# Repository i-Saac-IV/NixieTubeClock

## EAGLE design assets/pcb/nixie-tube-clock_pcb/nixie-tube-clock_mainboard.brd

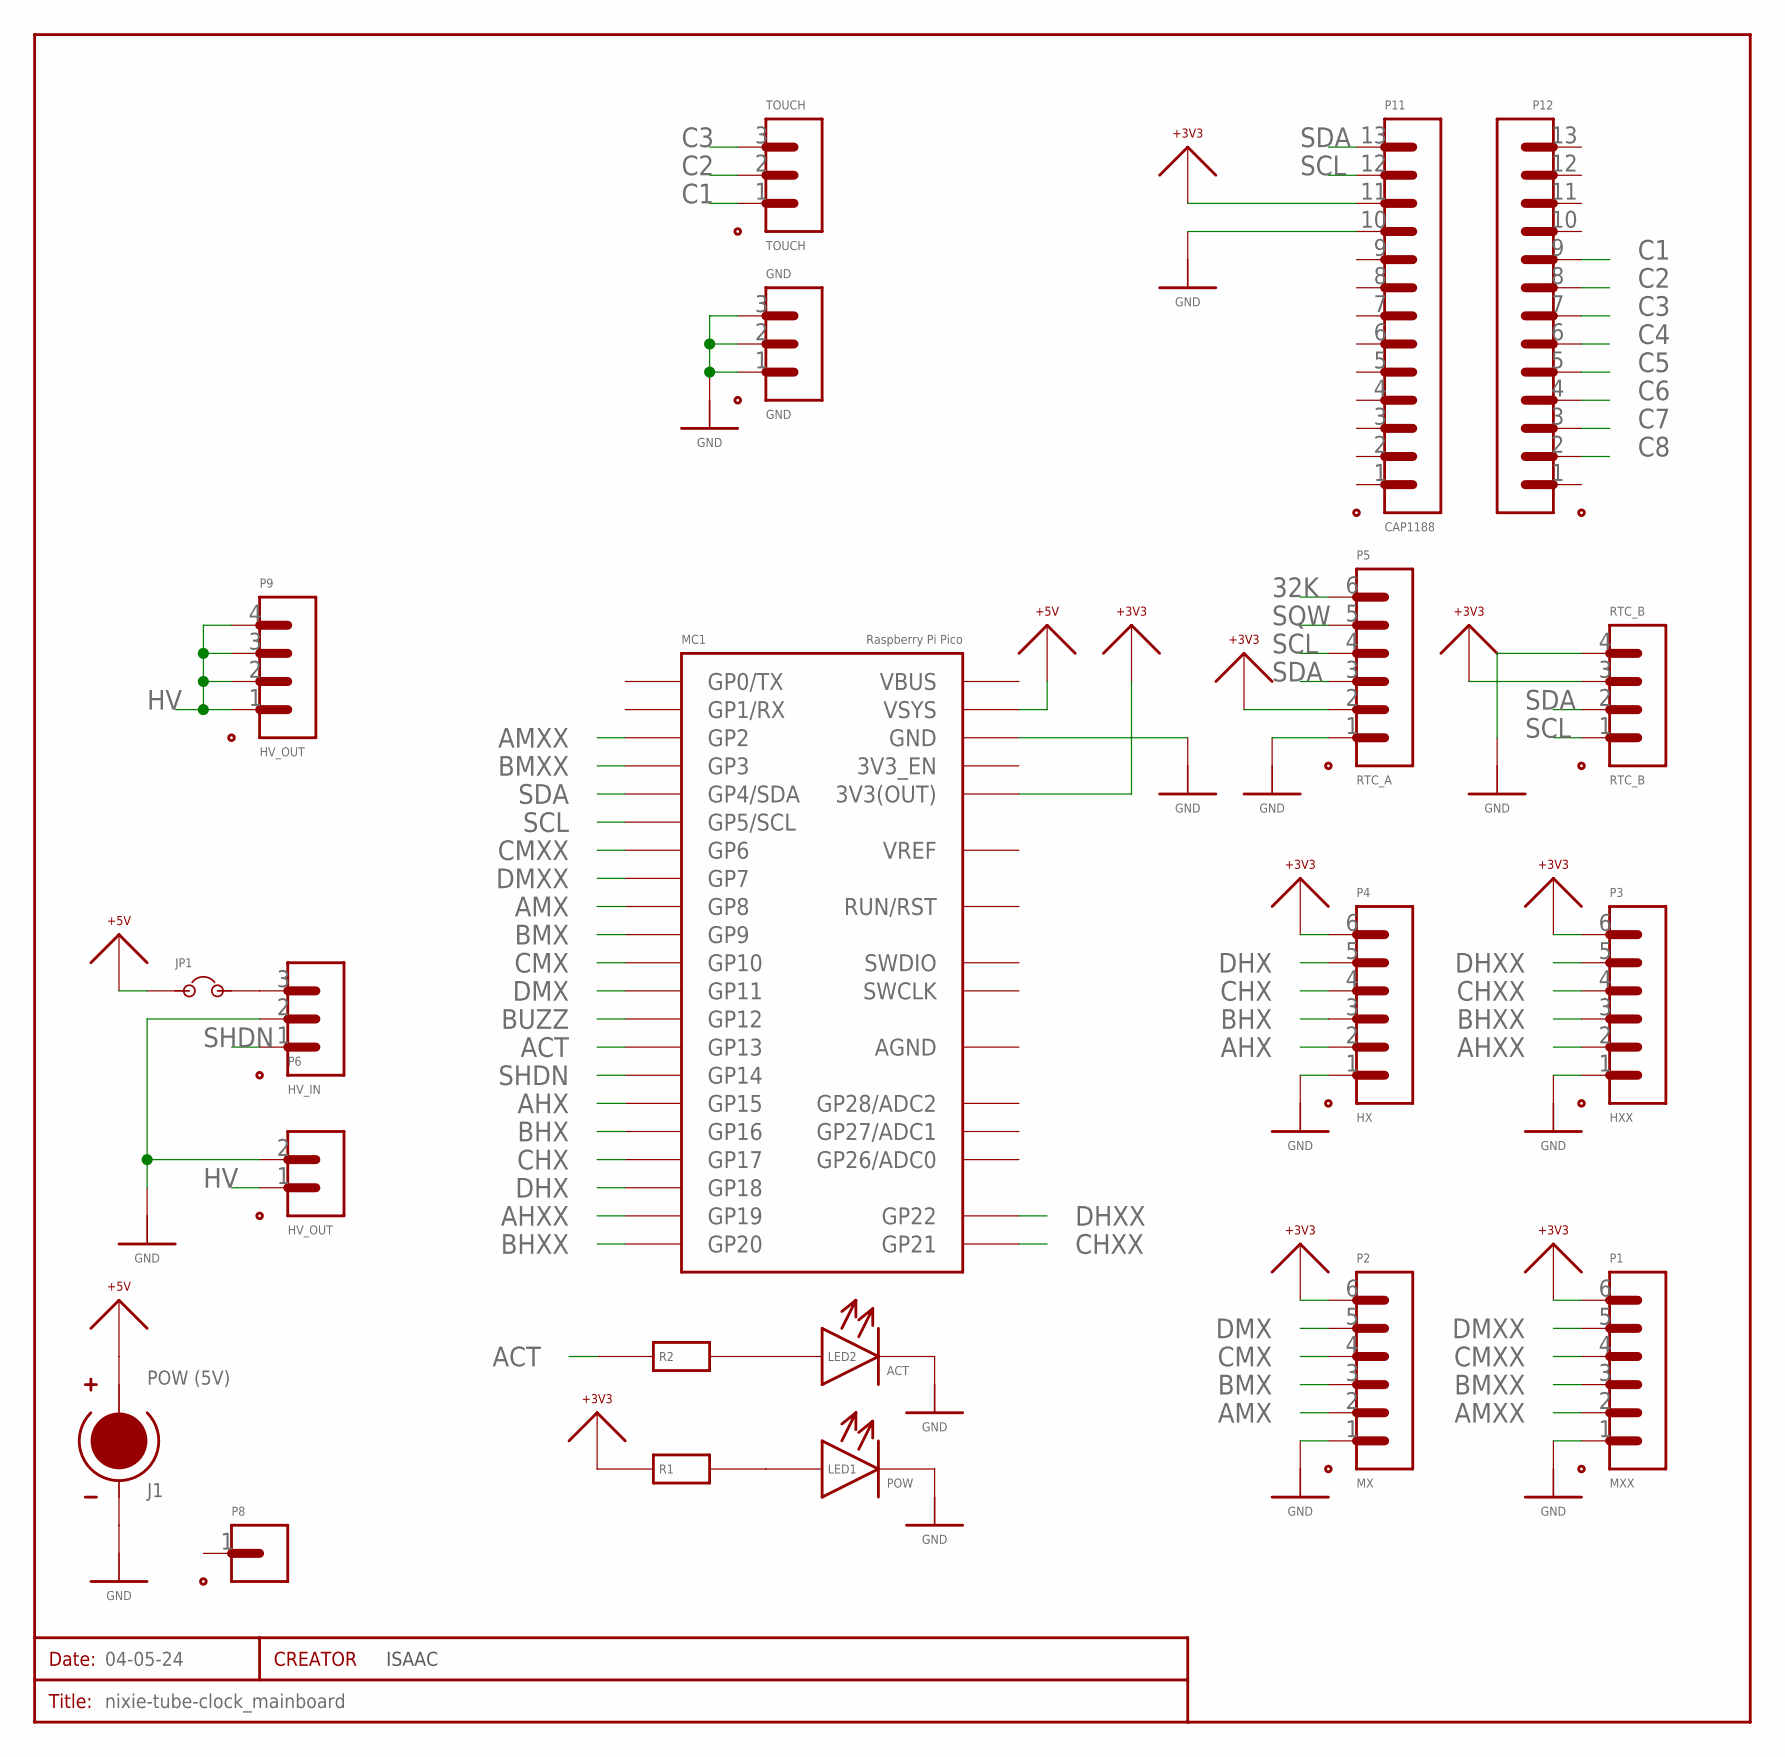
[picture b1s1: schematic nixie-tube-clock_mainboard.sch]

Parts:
CREATOR: ISAAC; INFO_T
GND: GND; XH2.54_3-PIN
J1: POW (5V); XH2.54_2-PIN
JP1: JUMPER_2-WAY_HEADER; HEADER_2-PIN_JUMPER
LED1: POW; LED_3MM
LED2: ACT; LED_3MM
MC1: RASPBERRY-PI-PICO_THT
P1: MXX; XH2.54_6-PIN
P2: MX; XH2.54_6-PIN
P3: HXX; XH2.54_6-PIN
P4: HX; XH2.54_6-PIN
P5: RTC_A; HEADER_6-PIN
P6: HV_OUT; HEADER_2-PIN
P7: HV_IN; HEADER_3-PIN
P8: PORT_1-PIN_HEADER; HEADER_1-PIN
P9: HV_OUT; XH2.54_4-PIN
P11: CAP1188; HEADER_13-PIN
P12: PORT_13-PIN_HEADER; HEADER_13-PIN
R1, R2: RESISTOR; RESISTOR_10.16MM
RTC_B: RTC_B; XH2.54_4-PIN
SCHEMATIC1: 04-05-24; SHEET
TOUCH: TOUCH; XH2.54_3-PIN

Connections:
32K: P5.6
+3V3: MC1.36 (3V3(OUT)), P1.6, P2.6, P3.6, P4.6, P5.2, P11.11, R1.1, RTC_B.3
+5V: J1.2 (+), JP1.1, MC1.39 (VSYS)
ACT: MC1.17 (GP13), R2.1
AGND: MC1.33 (AGND)
AHX: MC1.20 (GP15), P4.2
AHXX: MC1.25 (GP19), P3.2
AMX: MC1.11 (GP8), P2.2
AMXX: MC1.4 (GP2), P1.2
BHX: MC1.21 (GP16), P4.3
BHXX: MC1.26 (GP20), P3.3
BMX: MC1.12 (GP9), P2.3
BMXX: MC1.5 (GP3), P1.3
BUZZ: MC1.16 (GP12)
C1: P12.9, TOUCH.1
C2: P12.8, TOUCH.2
C3: P12.7, TOUCH.3
C4: P12.6
C5: P12.5
C6: P12.4
C7: P12.3
C8: P12.2
CHX: MC1.22 (GP17), P4.4
CHXX: MC1.27 (GP21), P3.4
CMX: MC1.14 (GP10), P2.4
CMXX: MC1.9 (GP6), P1.4
DHX: MC1.24 (GP18), P4.5
DHXX: MC1.29 (GP22), P3.5
DMX: MC1.15 (GP11), P2.5
DMXX: MC1.10 (GP7), P1.5
GND: GND.1, GND.2, GND.3, J1.1 (GND), LED1.-, LED2.-, MC1.3 (GND), MC1.8 (GND), MC1.13 (GND), MC1.18 (GND), MC1.23 (GND), MC1.28 (GND), MC1.38 (GND), MC1.D_GND (GND), P1.1, P2.1, P3.1, P4.1, P5.1, P6.2, P7.2, P11.10, RTC_B.4
HV: P6.1, P9.1, P9.2, P9.3, P9.4
unnamed: LED1.+, R1.2
unnamed: LED2.+, R2.2
unnamed: JP1.2, P7.3
SCL: MC1.7 (GP5/SCL), P5.4, P11.12, RTC_B.1
SDA: MC1.6 (GP4/SDA), P5.3, P11.13, RTC_B.2
SHDN: MC1.19 (GP14), P7.1
SQW: P5.5

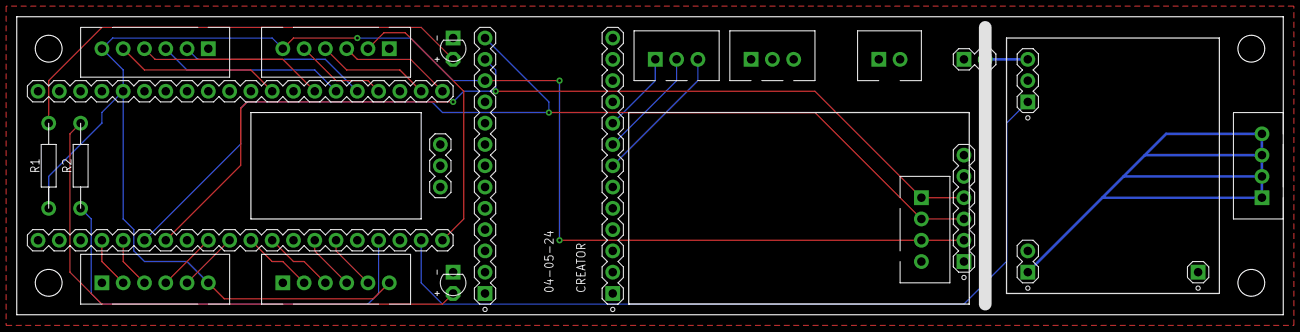
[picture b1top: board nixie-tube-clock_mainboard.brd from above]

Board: 2 copper layers, 151.1 x 35.6 mm, 23 parts (0 on the bottom side), 30 nets.

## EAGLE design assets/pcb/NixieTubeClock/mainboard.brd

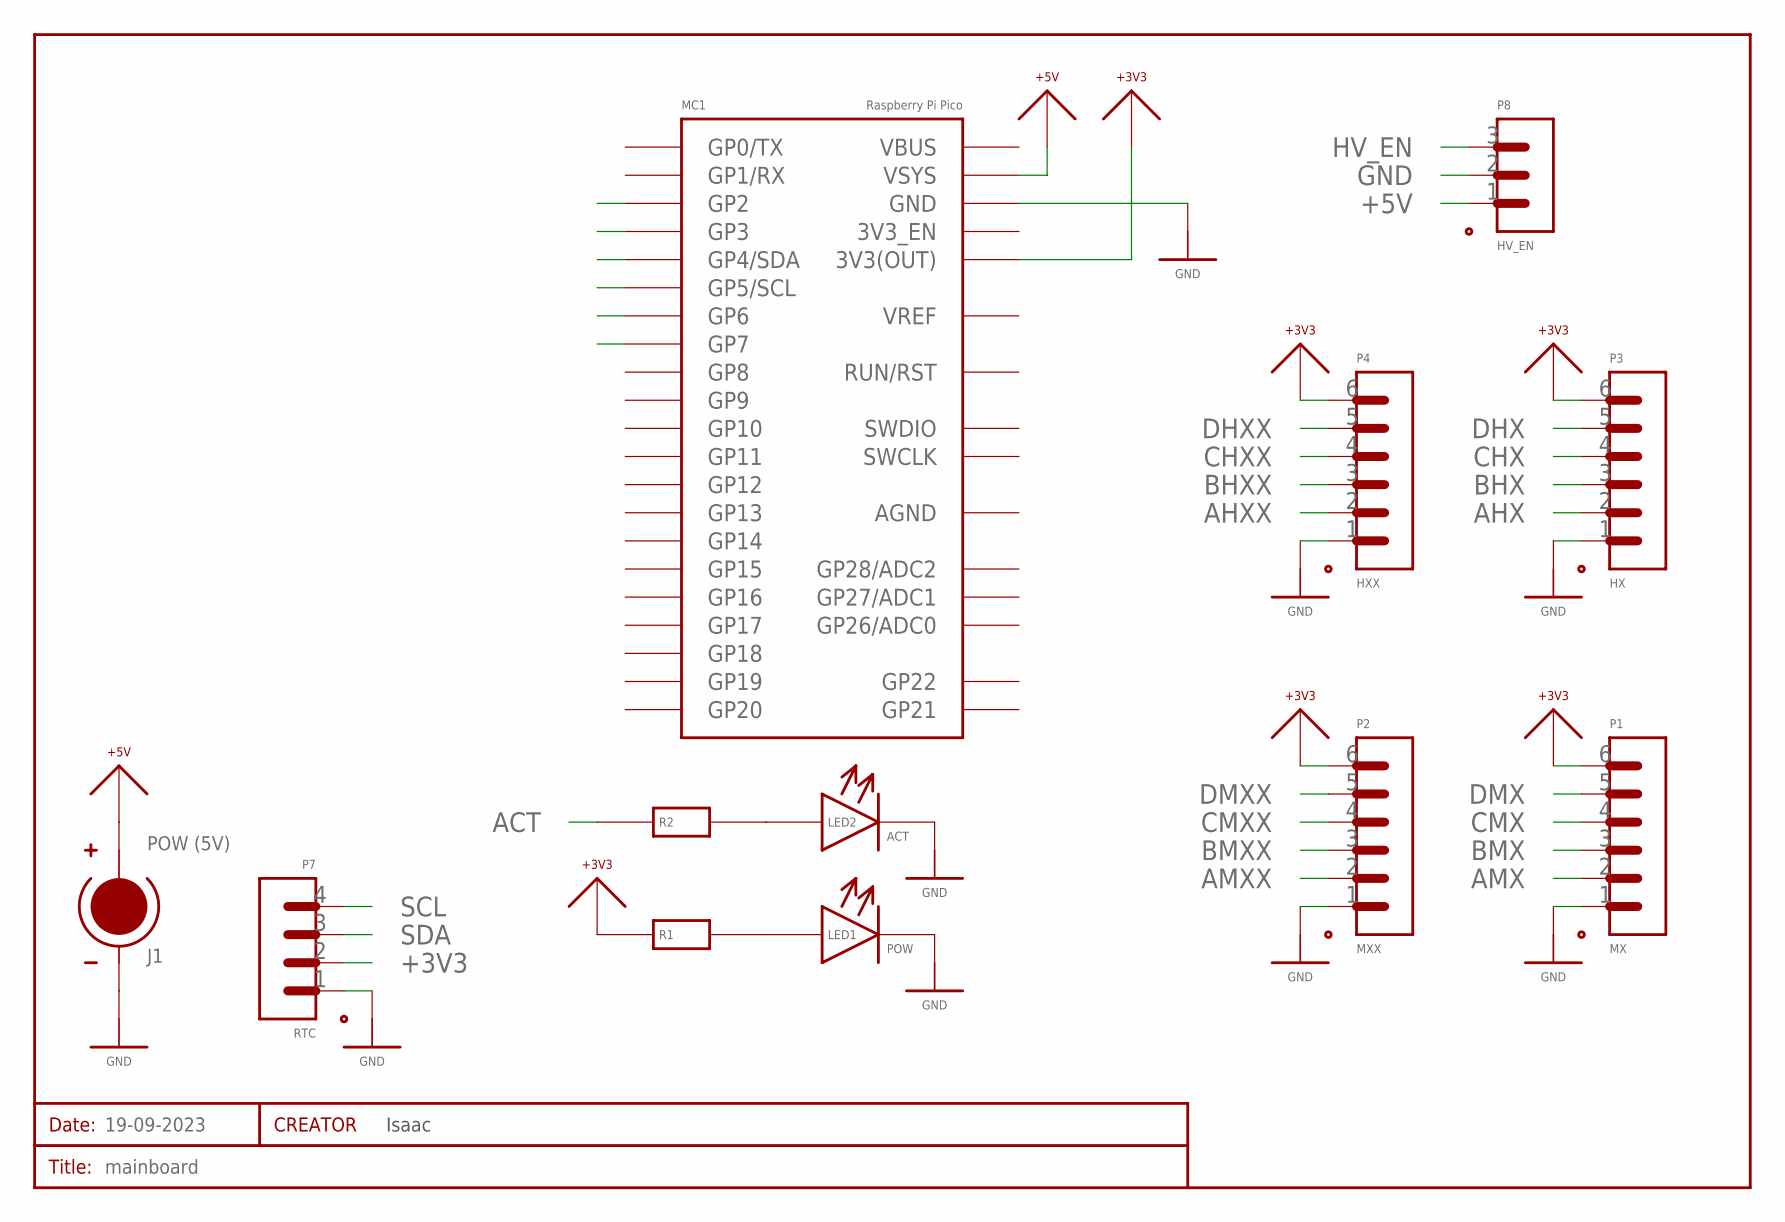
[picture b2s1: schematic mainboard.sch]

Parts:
CREATOR: Isaac; INFO_T
J1: POW (5V); XH2.54_2-PIN
LED1: POW; LED_3MM
LED2: ACT; LED_3MM
MC1: RASPBERRY-PI-PICO_THT
P1: MX; XH2.54_6-PIN
P2: MXX; XH2.54_6-PIN
P3: HX; XH2.54_6-PIN
P4: HXX; XH2.54_6-PIN
P7: RTC; XH2.54_4-PIN
P8: HV_EN; XH2.54_3-PIN
R1, R2: RESISTOR; RESISTOR_10.16MM
SCHEMATIC1: 19-09-2023; SHEET

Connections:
+3V3: MC1.36 (3V3(OUT)), P1.6, P2.6, P3.6, P4.6, P7.2, R1.1
+5V: J1.2 (+), MC1.39 (VSYS), P8.1
ACT: R2.1
AGND: MC1.33 (AGND)
AHX: P3.2
AHXX: P4.2
AMX: P1.2
AMXX: P2.2
BHX: P3.3
BHXX: P4.3
BMX: P1.3
BMXX: P2.3
CHX: P3.4
CHXX: P4.4
CMX: P1.4
CMXX: P2.4
DHX: P3.5
DHXX: P4.5
DMX: P1.5
DMXX: P2.5
GND: J1.1 (GND), LED1.-, LED2.-, MC1.3 (GND), MC1.8 (GND), MC1.13 (GND), MC1.18 (GND), MC1.23 (GND), MC1.28 (GND), MC1.38 (GND), MC1.D_GND (GND), P1.1, P2.1, P3.1, P4.1, P7.1, P8.2
HV_EN: P8.3
unnamed: LED1.+, R1.2
unnamed: LED2.+, R2.2
SCL: P7.4
SDA: P7.3

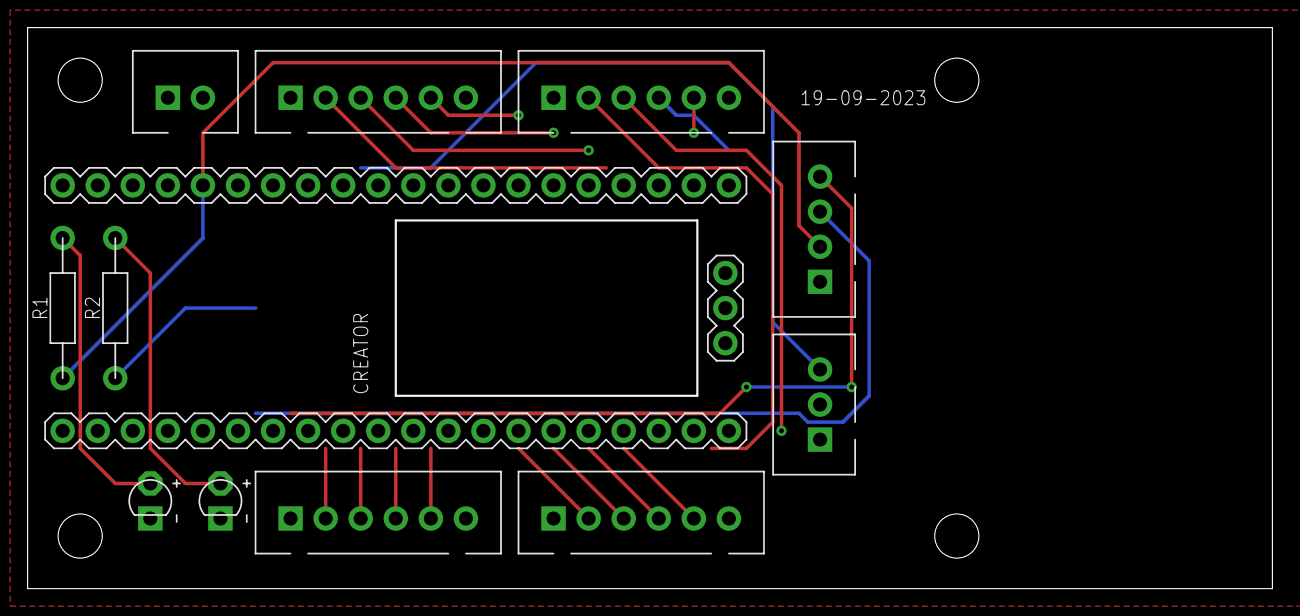
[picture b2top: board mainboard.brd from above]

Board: 2 copper layers, 90.0 x 40.5 mm, 14 parts (0 on the bottom side), 5 nets.

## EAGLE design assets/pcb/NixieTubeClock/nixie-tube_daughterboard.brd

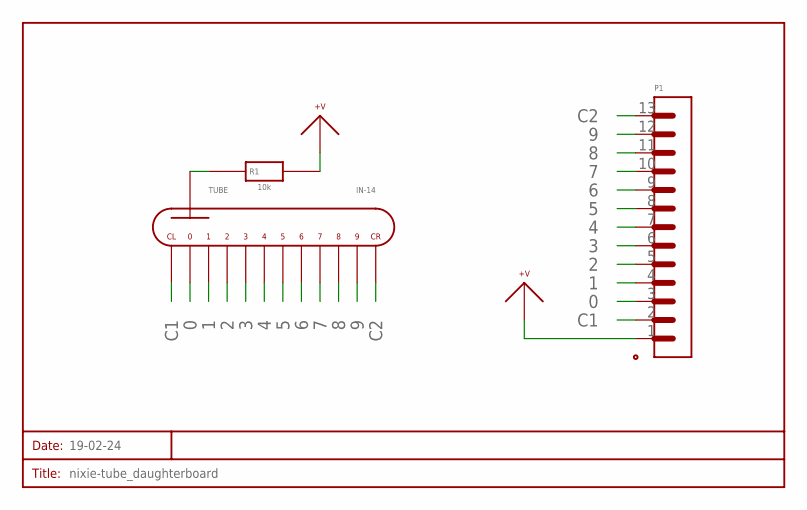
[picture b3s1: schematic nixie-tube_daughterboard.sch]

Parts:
P1: PORT_13-PIN_HEADER; HEADER_13-PIN
R1: 10k; RESISTOR_10.16MM
SCHEMATIC1: 19-02-24; SHEET
TUBE: IN-14; NIXIE-TUBE_IN-14

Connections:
0: P1.3, TUBE.0
1: P1.4, TUBE.1
2: P1.5, TUBE.2
3: P1.6, TUBE.3
4: P1.7, TUBE.4
5: P1.8, TUBE.5
6: P1.9, TUBE.6
7: P1.10, TUBE.7
8: P1.11, TUBE.8
9: P1.12, TUBE.9
+V: P1.1, R1.2
C1: P1.2, TUBE.C1
C2: P1.13, TUBE.C2
unnamed: R1.1, TUBE.A (ANODE)

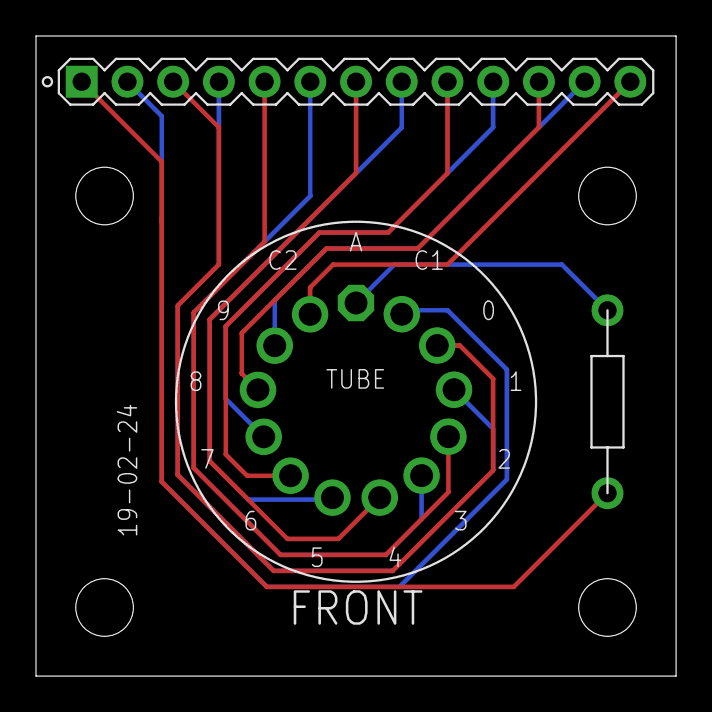
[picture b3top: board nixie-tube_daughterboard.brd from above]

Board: 2 copper layers, 35.6 x 35.6 mm, 4 parts (0 on the bottom side), 14 nets.

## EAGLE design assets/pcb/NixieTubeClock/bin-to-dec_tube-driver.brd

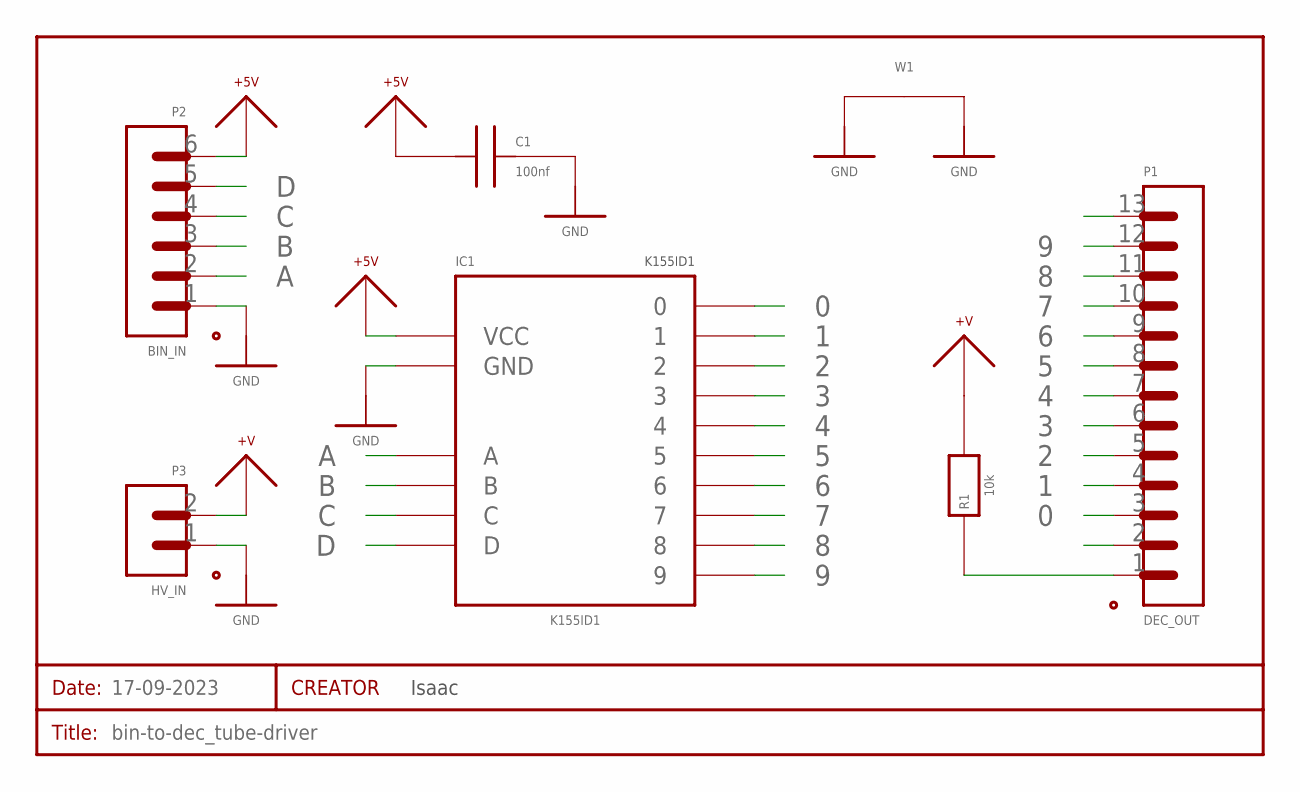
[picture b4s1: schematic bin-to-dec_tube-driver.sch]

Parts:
C1: 100nf; CAPACITOR_UNPOLARISED_5.08MM
CREATOR: Isaac; INFO_T
IC1: K155ID1; 16-PIN_DIP
P1: DEC_OUT; HEADER_13-PIN
P2: BIN_IN; XH2.54_6-PIN
P3: HV_IN; XH2.54_2-PIN
R1: 10k; RESISTOR_10.16MM
SCHEMATIC1: 17-09-2023; SHEET
W1: WIRE_7.62MM

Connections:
0: IC1.16 (0), P1.3
1: IC1.15 (1), P1.4
2: IC1.8 (2), P1.5
3: IC1.9 (3), P1.6
4: IC1.13 (4), P1.7
5: IC1.14 (5), P1.8
6: IC1.11 (6), P1.9
7: IC1.10 (7), P1.10
8: IC1.1 (8), P1.11
9: IC1.2 (9), P1.12
+5V: C1.1, IC1.5 (VCC), P2.6
+V: P3.2, R1.2
A: IC1.3 (A), P2.2
B: IC1.6 (B), P2.3
C: IC1.7 (C), P2.4
D: IC1.4 (D), P2.5
GND: C1.2, IC1.12 (GND), P2.1, P3.1, W1.1, W1.2
unnamed: P1.1, R1.1

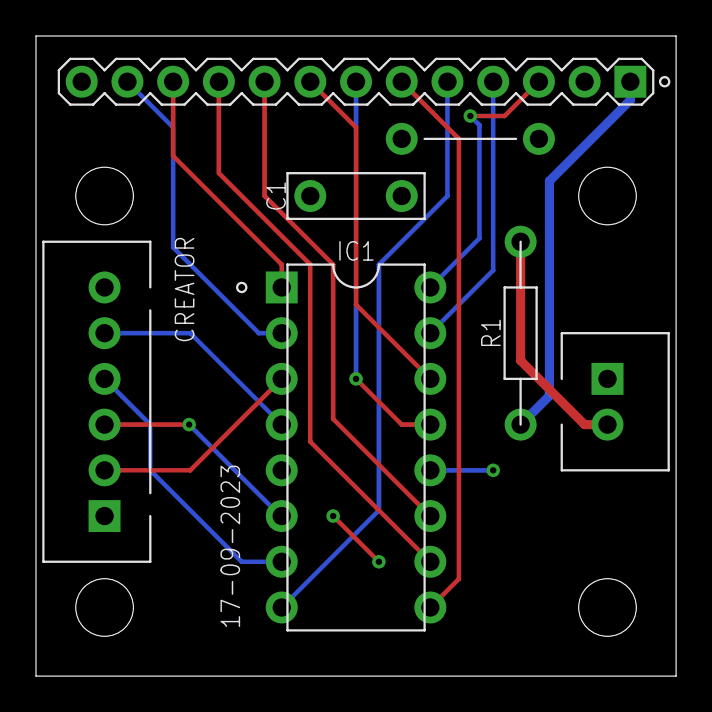
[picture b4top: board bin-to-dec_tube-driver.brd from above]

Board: 2 copper layers, 35.6 x 35.6 mm, 9 parts (0 on the bottom side), 18 nets.

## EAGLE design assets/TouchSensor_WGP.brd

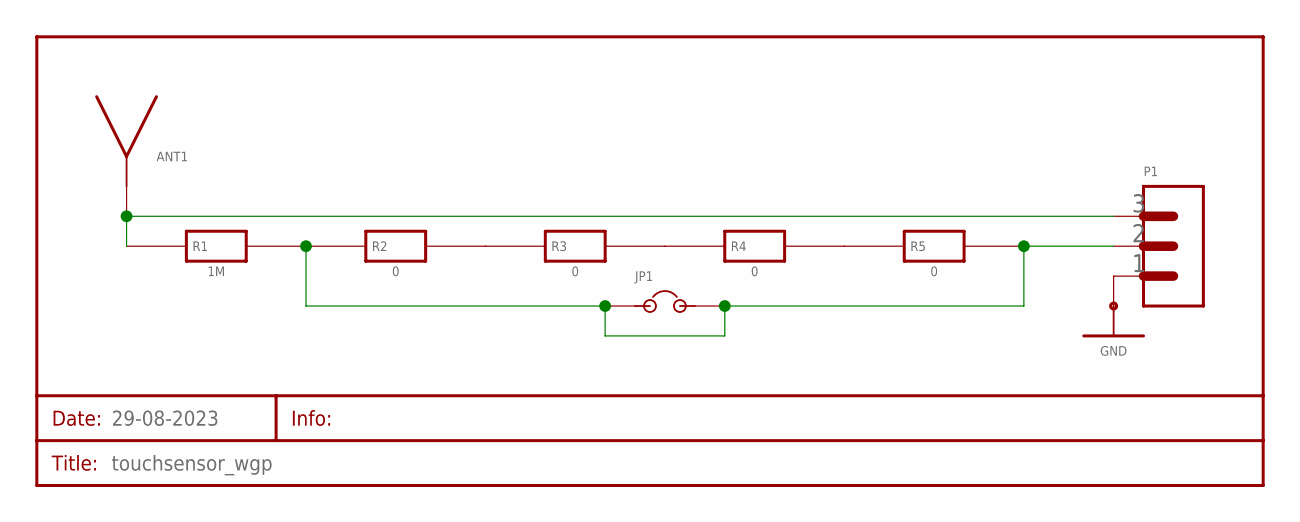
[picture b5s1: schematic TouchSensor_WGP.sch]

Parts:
JP1: JUMPER_2-WAY_PCB_B; PCB_JUMPER_2-WAY_B
P1: PORT_3_PIN_HEADER; HEADER_3_PIN
R1: 1M; RESISTOR_10.16MM
R2, R3, R4, R5: 0; RESISTOR_10.16MM
SCHEMATIC1: 29-08-2023; SHEET

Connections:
ANT: P1.3, R1.1
GND: P1.1
unnamed: R2.2, R3.1
unnamed: R3.2, R4.1
unnamed: R4.2, R5.1
unnamed: JP1.1, JP1.2, P1.2, R1.2, R2.1, R5.2

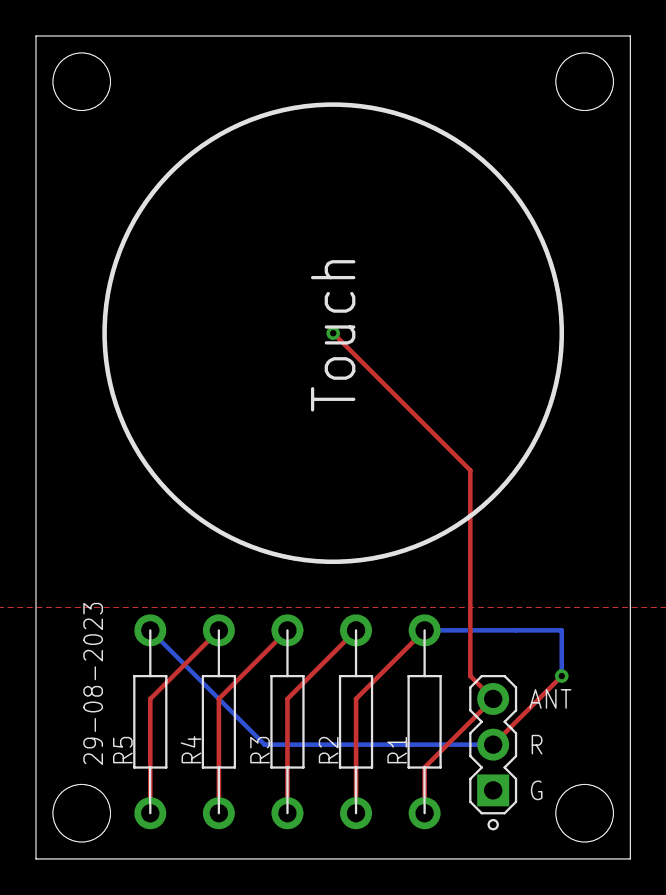
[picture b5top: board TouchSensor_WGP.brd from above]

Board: 2 copper layers, 33.0 x 45.7 mm, 8 parts (0 on the bottom side), 5 nets.

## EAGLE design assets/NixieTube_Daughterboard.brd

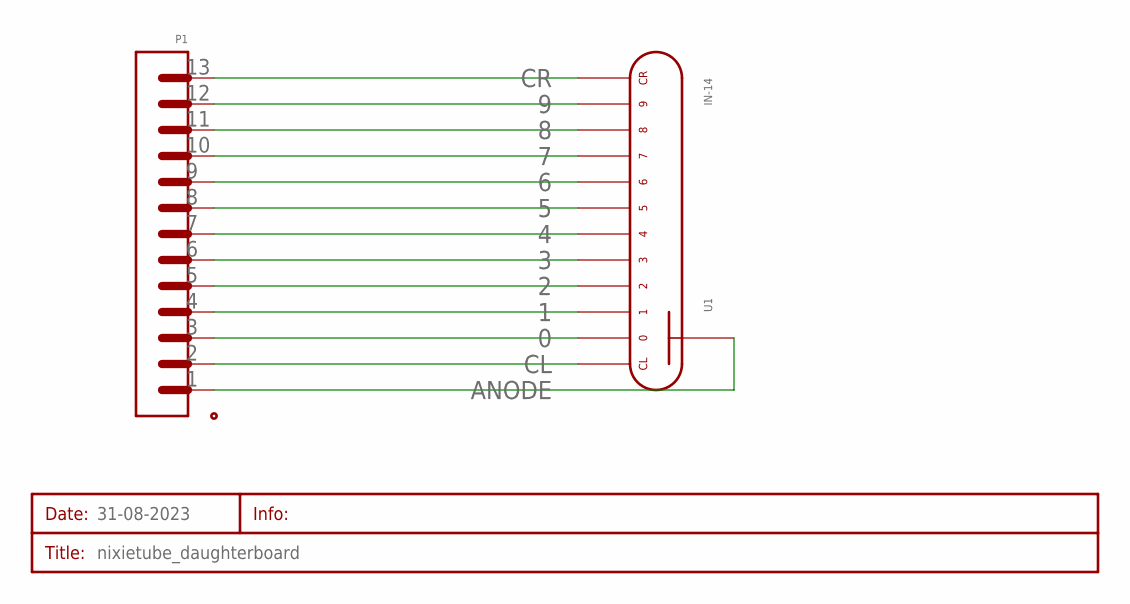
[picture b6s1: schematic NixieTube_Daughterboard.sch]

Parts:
P1: PORT_13-PIN_XH2.54; XH2.54_13-PIN
SCHEMATIC1: 31-08-2023; SHEET
U1: IN-14; NIXIE-TUBE_IN-14

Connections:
0: P1.3, U1.1 (0)
1: P1.4, U1.2 (1)
2: P1.5, U1.3 (2)
3: P1.6, U1.4 (3)
4: P1.7, U1.5 (4)
5: P1.8, U1.6 (5)
6: P1.9, U1.7 (6)
7: P1.10, U1.8 (7)
8: P1.11, U1.9 (8)
9: P1.12, U1.0 (9)
ANODE: P1.1, U1.A (ANODE)
CL: P1.2, U1.C1
CR: P1.13, U1.C2

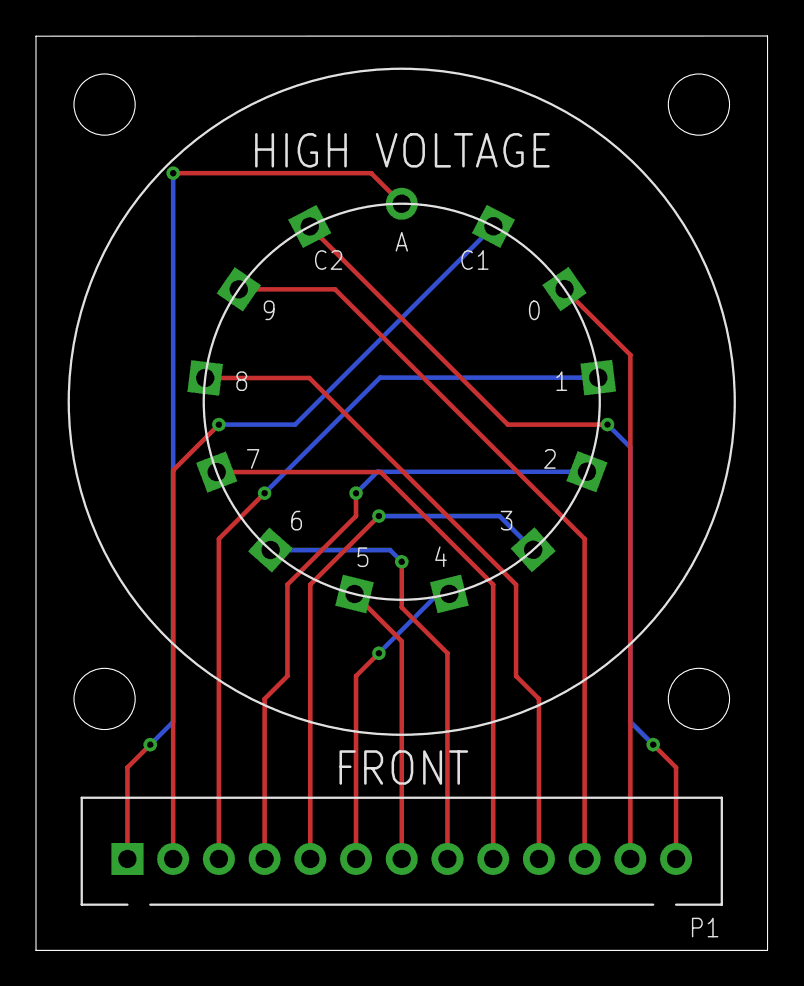
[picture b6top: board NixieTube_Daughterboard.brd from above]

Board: 2 copper layers, 40.6 x 50.8 mm, 3 parts (0 on the bottom side), 13 nets.

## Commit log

2023-09-10 first commit - committing all files
2023-09-10 Delete README.md
    I think i need to create it in a different way
2023-09-12 adding new test file and beginning to reverse engineer the CapSense library
2023-09-17 deleting old files
2023-09-17 update ignore file
2023-09-19 adding pcb files
2023-09-19 code update
2024-04-12 adding top of housing
2024-04-12 updates to PCB
2024-04-12 updated housing
2024-05-04 cleaned up files
2024-05-04 updated pin assignments
2024-05-04 created v1 of mainboard
